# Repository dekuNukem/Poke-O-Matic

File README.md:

This is the PCB version of Poke-O-Matic. This project in unmaintained since PowerSave came out, but feel free to take a look at the code.

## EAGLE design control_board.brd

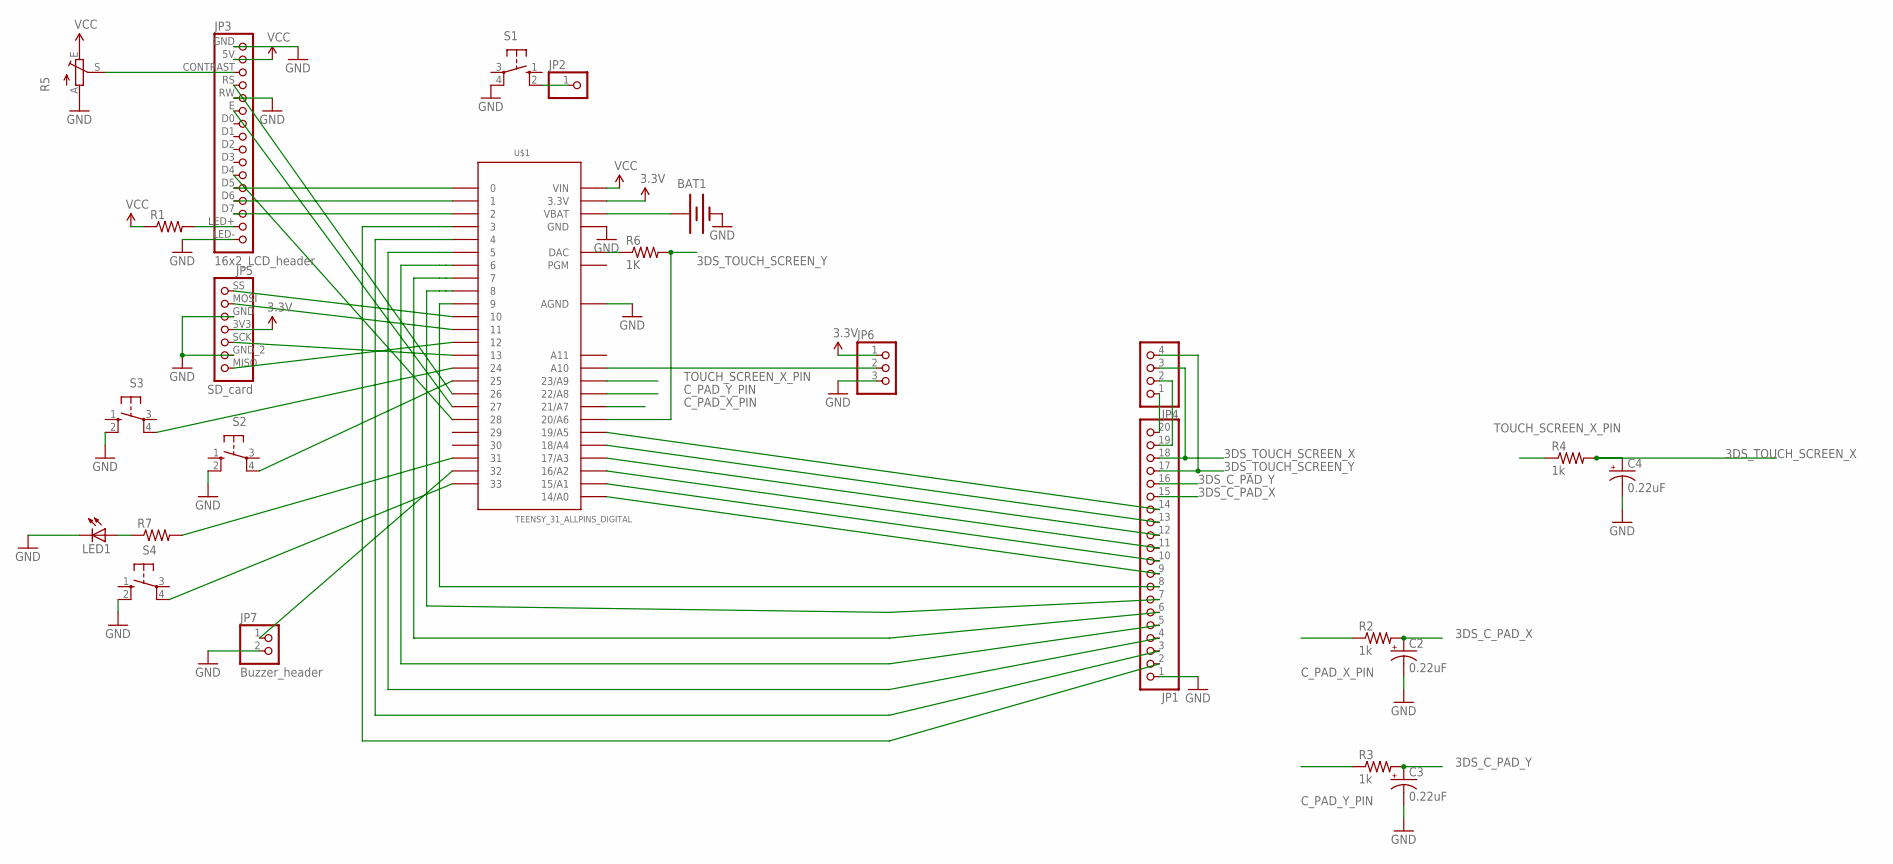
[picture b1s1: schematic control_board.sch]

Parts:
BAT1: BATTERY20PTH; BATTCOM_20MM_PTH
C2, C3, C4: 0.22uF; CPOL-RADIAL-10UF-25V
JP1: PINHD-1X20; 1X20
JP2: PINHD-1X1; 1X01
JP3: 16x2_LCD_header; 1X16
JP4: PINHD-1X4; 1X04
JP5: SD_card; 1X07
JP6: PINHD-1X3; 1X03
JP7: Buzzer_header; 1X02
LED1: LED5MM
R1, R7: RESISTOREZ; AXIAL-0.3EZ
R2, R3, R4: 1k; AXIAL-0.1
R5: TRIM_EU-CA6V; CA6V
R6: 1K; AXIAL-0.1
S1, S2, S3, S4: 10-XX; B3F-10XX
U$1: TEENSY_31_ALLPINS_DIGITAL

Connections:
3.3V: JP5.3V3 (4), JP6.1, U$1.3.3V
3DS_C_PAD_X: C2.1 (+), JP1.15, R2.P$2 (2)
3DS_C_PAD_Y: C3.1 (+), JP1.16, R3.P$2 (2)
3DS_TOUCH_SCREEN_X: C4.1 (+), JP1.18, JP4.3, R4.P$2 (2)
3DS_TOUCH_SCREEN_Y: JP1.17, JP4.4, R6.P$2 (2), U$1.20/A6
C_PAD_X_PIN: R2.P$1 (1), U$1.21/A7
C_PAD_Y_PIN: R3.P$1 (1), U$1.22/A8
GND: BAT1.2 (-), C2.2 (-), C3.2 (-), C4.2 (-), JP1.1, JP3.GND, JP3.LED-, JP3.RW, JP5.GND (3), JP5.GND_2 (6), JP6.3, JP7.2, LED1.K (C), R5.A, S1.4 (P1), S2.2 (S1), S3.2 (S1), S4.2 (S1), U$1.AGND, U$1.GND
unnamed: JP1.7, U$1.8
unnamed: JP1.8, U$1.9
unnamed: JP1.9, U$1.14/A0
unnamed: JP1.10, U$1.15/A1
unnamed: JP1.11, U$1.16/A2
unnamed: JP1.12, U$1.17/A3
unnamed: JP1.13, U$1.18/A4
unnamed: JP1.14, U$1.19/A5
unnamed: JP3.LED+, R1.P$2 (2)
unnamed: JP3.CONTRAST, R5.S
unnamed: JP5.SS (1), U$1.10
unnamed: JP5.MOSI (2), U$1.11
unnamed: JP5.MISO (7), U$1.12
unnamed: JP2.1, S1.2 (S1)
unnamed: JP5.SCK (5), U$1.13
unnamed: JP6.2, U$1.A10
unnamed: JP3.D7, U$1.2
unnamed: JP3.D6, U$1.1
unnamed: JP3.D5, U$1.0
unnamed: JP3.D4, U$1.28
unnamed: JP3.E, U$1.27
unnamed: JP1.2, U$1.3
unnamed: JP1.3, U$1.4
unnamed: JP1.4, U$1.5
unnamed: JP1.5, U$1.6
unnamed: JP1.6, U$1.7
unnamed: R6.P$1 (1), U$1.RESET (DAC)
unnamed: JP3.RS, U$1.26
unnamed: BAT1.1 (+), U$1.VBAT
unnamed: S2.4 (P1), U$1.25
unnamed: S3.4 (P1), U$1.24
unnamed: S4.4 (P1), U$1.33
unnamed: R7.P$2 (2), U$1.31
unnamed: JP1.20, JP4.1
unnamed: JP1.19, JP4.2
unnamed: LED1.A, R7.P$1 (1)
unnamed: JP7.1, U$1.32
TOUCH_SCREEN_X_PIN: R4.P$1 (1), U$1.23/A9
VCC: JP3.5V, R1.P$1 (1), R5.E, U$1.VIN

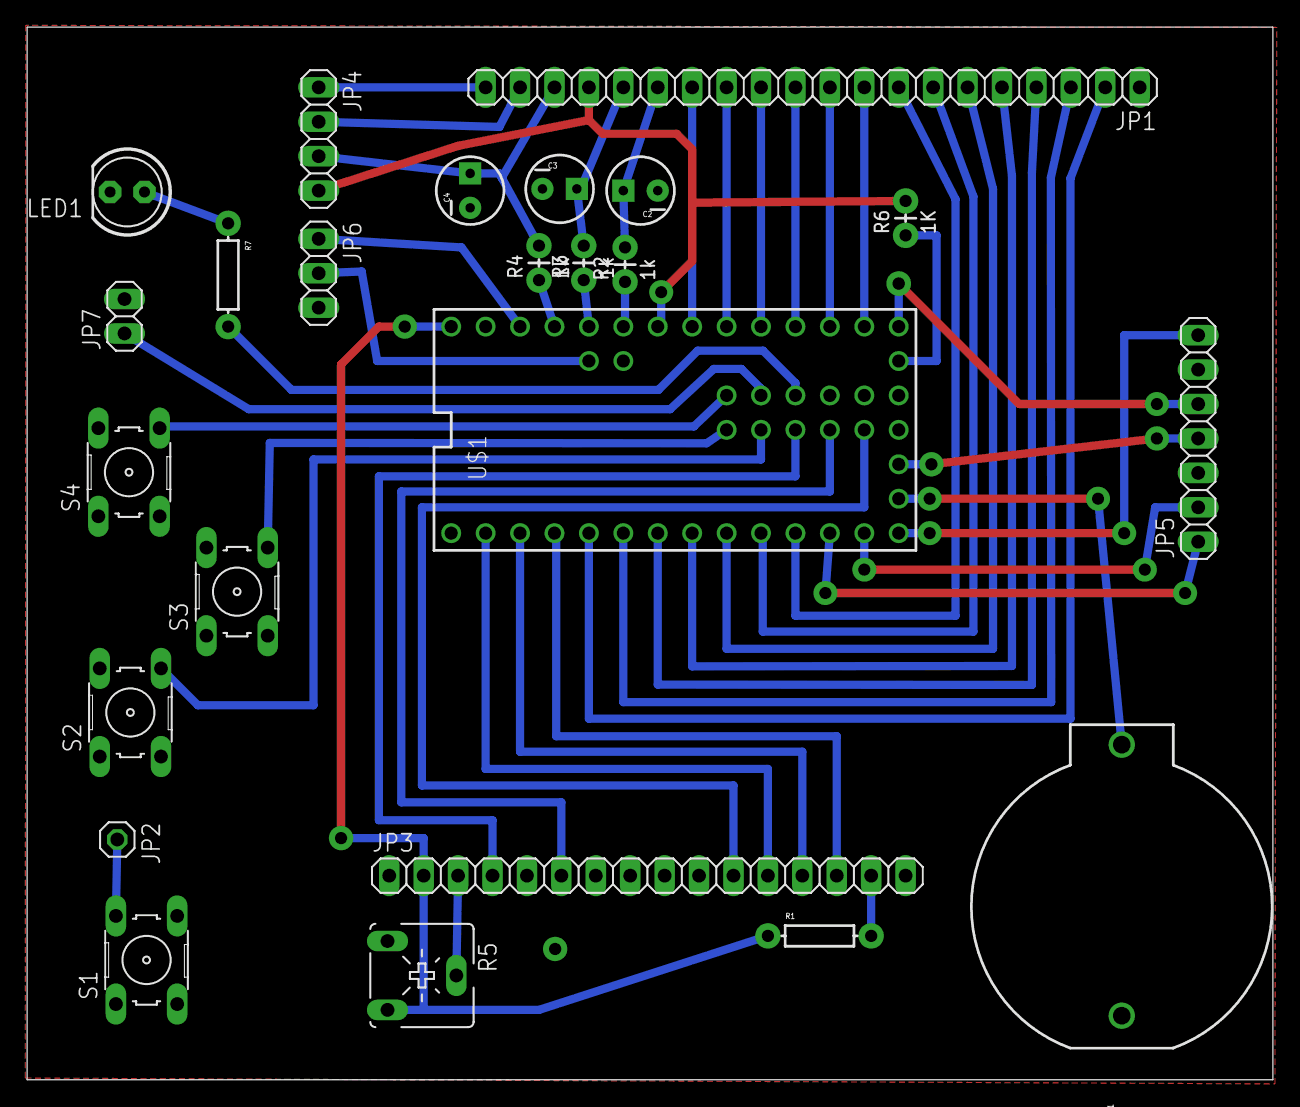
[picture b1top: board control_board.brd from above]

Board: 2 copper layers, 91.9 x 77.7 mm, 24 parts (0 on the bottom side), 47 nets.

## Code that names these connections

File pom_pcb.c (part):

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#define DS_SELECT_BUTTON_PIN UNDEFINED
#define POWER_BUTTON_PIN 3

#define TOUCH_SCREEN_X_PIN 23
#define TOUCH_SCREEN_Y_PIN A14
#define TOUCH_SCREEN_Y_SENSE_PIN 19
#define C_PAD_X_PIN 21
#define C_PAD_Y_PIN 22
#define LIGHT_SENSOR_PIN A10
#define AUDIO_IN_PIN UNDEFINED
#define BUZZER_PIN 32
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	lcd.begin(16, 2);
	analogReadResolution(10);
	analogWriteResolution(9);
	pinMode(TOUCH_SCREEN_X_PIN, INPUT);
	pinMode(TOUCH_SCREEN_Y_PIN, INPUT);
	pinMode(TOUCH_SCREEN_Y_SENSE_PIN, INPUT);
	pinMode(BUZZER_PIN, OUTPUT);
	pinMode(BLUE_LED_PIN, OUTPUT);
	pinMode(C_PAD_X_PIN, OUTPUT);
	pinMode(C_PAD_Y_PIN, OUTPUT);
	c_pad_reset();
	do_UI();
	CLEAR_LCD();
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
void c_pad_reset()
{
	analogWrite(C_PAD_X_PIN, C_PAD_DEFAULT_POTENTIAL);
	analogWrite(C_PAD_Y_PIN, C_PAD_DEFAULT_POTENTIAL);
}

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

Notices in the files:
parts and their libraries:
SparkFun-Capacitors: Licensing: Creative Commons ShareAlike 4.0 International - https://creativecommons.org/licenses/by-sa/4.0
